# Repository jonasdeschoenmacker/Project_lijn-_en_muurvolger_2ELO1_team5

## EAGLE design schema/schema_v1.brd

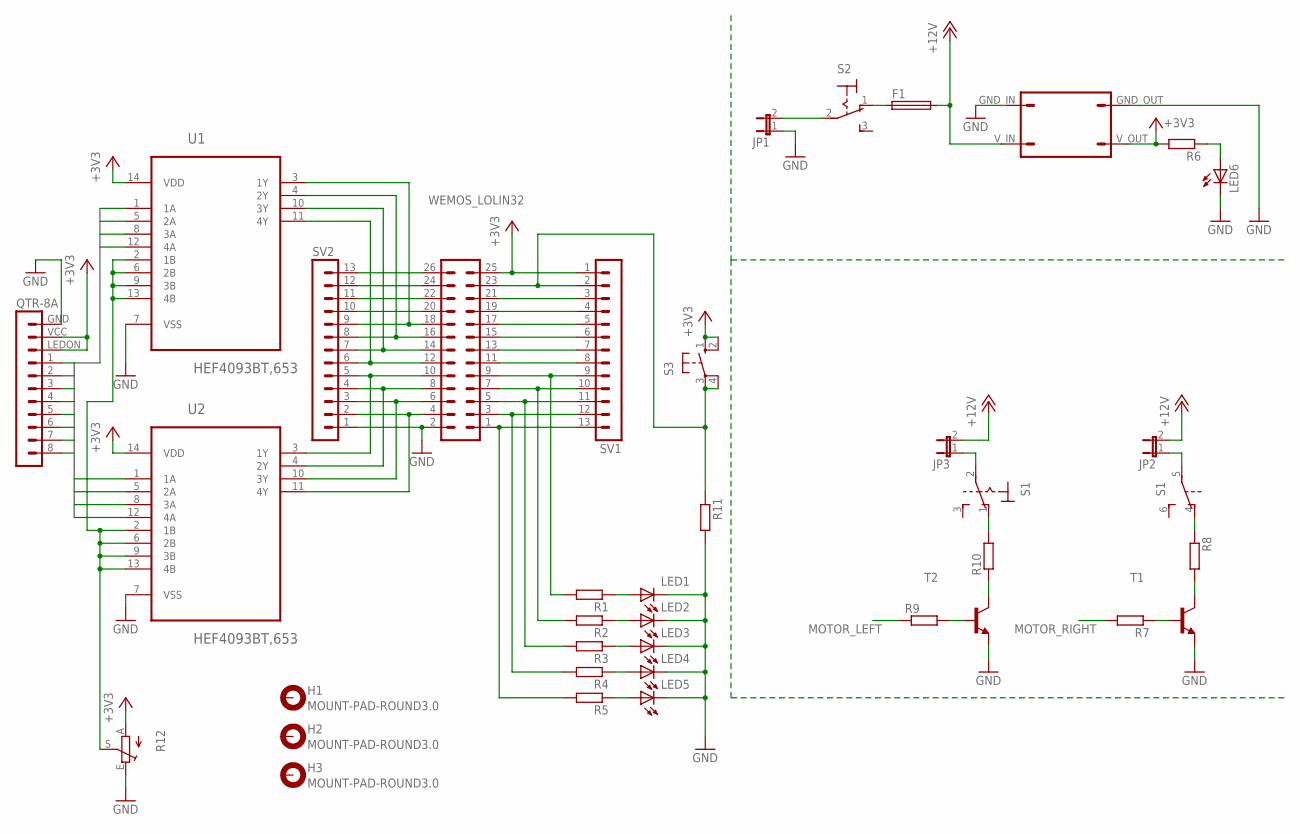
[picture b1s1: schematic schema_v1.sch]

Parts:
F1: SH22,5A
H1, H2, H3: MOUNT-PAD-ROUND3.0; 3,0-PAD
JP1, JP2, JP3: JP1E; JP1
LED1, LED2, LED3, LED4, LED5, LED6: LEDSMT1206; 1206
QTR-8A: WEMOS-LOLIN32_QTR-8A; WEMOS-LOLIN32_MA10-1
R1, R2, R3, R4, R5, R6, R7, R8, R9, R10, R11: R-EU_M0805; M0805
R12: POT_TRIM_EU-CA6V; POT_CA6V
S1: SWITCH_320-938
S2: SWITCH_320-916
S3: SWITCH-OMRON_10-XX; SWITCH-OMRON_B3F-10XX
SV1, SV2: MA13-1
T1, T2: TRANSISTOR-NPN-LINE-FOLLOWER_2N2222; TRANSISTOR-NPN-LINE-FOLLOWER_TO92-CBE
U1, U2: HEF4093BT,653; SOIC127P600X175-14N
U$2: COMPONENTEN-AANMAKEN_BUCK-CONVERTER; COMPONENTEN-AANMAKEN_MA04-1_BUCK
WEMOS_LOLIN32: WEMOS-LOLIN32_WEMOS_LOLIN32; WEMOS-LOLIN32_MA13-2

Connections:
+3V3: QTR-8A.LEDON, QTR-8A.VCC, R6.2, R12.A, S3.1 (S), S3.2 (S1), SV1.1, U1.14 (VDD), U2.14 (VDD), U$2.V_OUT, WEMOS_LOLIN32.25
+12V: F1.2, JP2.2, JP3.2, U$2.V_IN
ANALOG_BUS1: QTR-8A.1, U1.1 (1A)
ANALOG_BUS2: QTR-8A.2, U1.5 (2A)
ANALOG_BUS3: QTR-8A.3, U1.8 (3A)
ANALOG_BUS4: QTR-8A.4, U1.12 (4A)
ANALOG_BUS5: QTR-8A.5, U2.1 (1A)
ANALOG_BUS6: QTR-8A.6, U2.5 (2A)
ANALOG_BUS7: QTR-8A.7, U2.8 (3A)
ANALOG_BUS8: QTR-8A.8, U2.12 (4A)
GND: JP1.1, LED1.C, LED2.C, LED3.C, LED4.C, LED5.C, LED6.C, QTR-8A.GND, R11.2, R12.E, SV2.1, T1.E, T2.E, U1.7 (VSS), U2.7 (VSS), U$2.GND_IN, U$2.GND_OUT, WEMOS_LOLIN32.2
MOTOR_LEFT: R9.1, SV1.6, WEMOS_LOLIN32.15
MOTOR_RIGHT: R7.2, SV1.7, WEMOS_LOLIN32.13
unnamed: JP1.2, S2.2
unnamed: F1.1, S2.1 (O)
unnamed: SV2.9, U1.3 (1Y), WEMOS_LOLIN32.18
unnamed: LED6.A, R6.1
unnamed: SV2.8, U1.4 (2Y), WEMOS_LOLIN32.16
unnamed: SV2.7, U1.10 (3Y), WEMOS_LOLIN32.14
unnamed: SV2.6, U1.11 (4Y), WEMOS_LOLIN32.12
unnamed: SV2.2, U2.11 (4Y), WEMOS_LOLIN32.4
unnamed: LED1.A, R1.1
unnamed: LED2.A, R2.1
unnamed: LED3.A, R3.1
unnamed: LED4.A, R4.1
unnamed: LED5.A, R5.1
unnamed: R11.1, S3.3, S3.4 (P1), SV1.2, WEMOS_LOLIN32.23
unnamed: JP3.1, S1.2
unnamed: R10.2, S1.1 (O)
unnamed: R10.1, T2.C
unnamed: R9.2, T2.B
unnamed: JP2.1, S1.5
unnamed: R8.1, S1.4 (O)
unnamed: R8.2, T1.C
unnamed: R7.1, T1.B
unnamed: SV2.3, U2.10 (3Y), WEMOS_LOLIN32.6
unnamed: SV2.4, U2.4 (2Y), WEMOS_LOLIN32.8
unnamed: SV2.5, U2.3 (1Y), WEMOS_LOLIN32.10
unnamed: SV2.10, WEMOS_LOLIN32.20
unnamed: SV2.11, WEMOS_LOLIN32.22
unnamed: SV2.12, WEMOS_LOLIN32.24
unnamed: SV2.13, WEMOS_LOLIN32.26
unnamed: R5.2, SV1.13, WEMOS_LOLIN32.1
unnamed: R12.S, U1.2 (1B), U1.6 (2B), U1.9 (3B), U1.13 (4B), U2.2 (1B), U2.6 (2B), U2.9 (3B), U2.13 (4B)
unnamed: R4.2, SV1.12, WEMOS_LOLIN32.3
unnamed: R3.2, SV1.11, WEMOS_LOLIN32.5
unnamed: R2.2, SV1.10, WEMOS_LOLIN32.7
unnamed: R1.2, SV1.9, WEMOS_LOLIN32.9
unnamed: SV1.3, WEMOS_LOLIN32.21
unnamed: SV1.4, WEMOS_LOLIN32.19
unnamed: SV1.5, WEMOS_LOLIN32.17
unnamed: SV1.8, WEMOS_LOLIN32.11

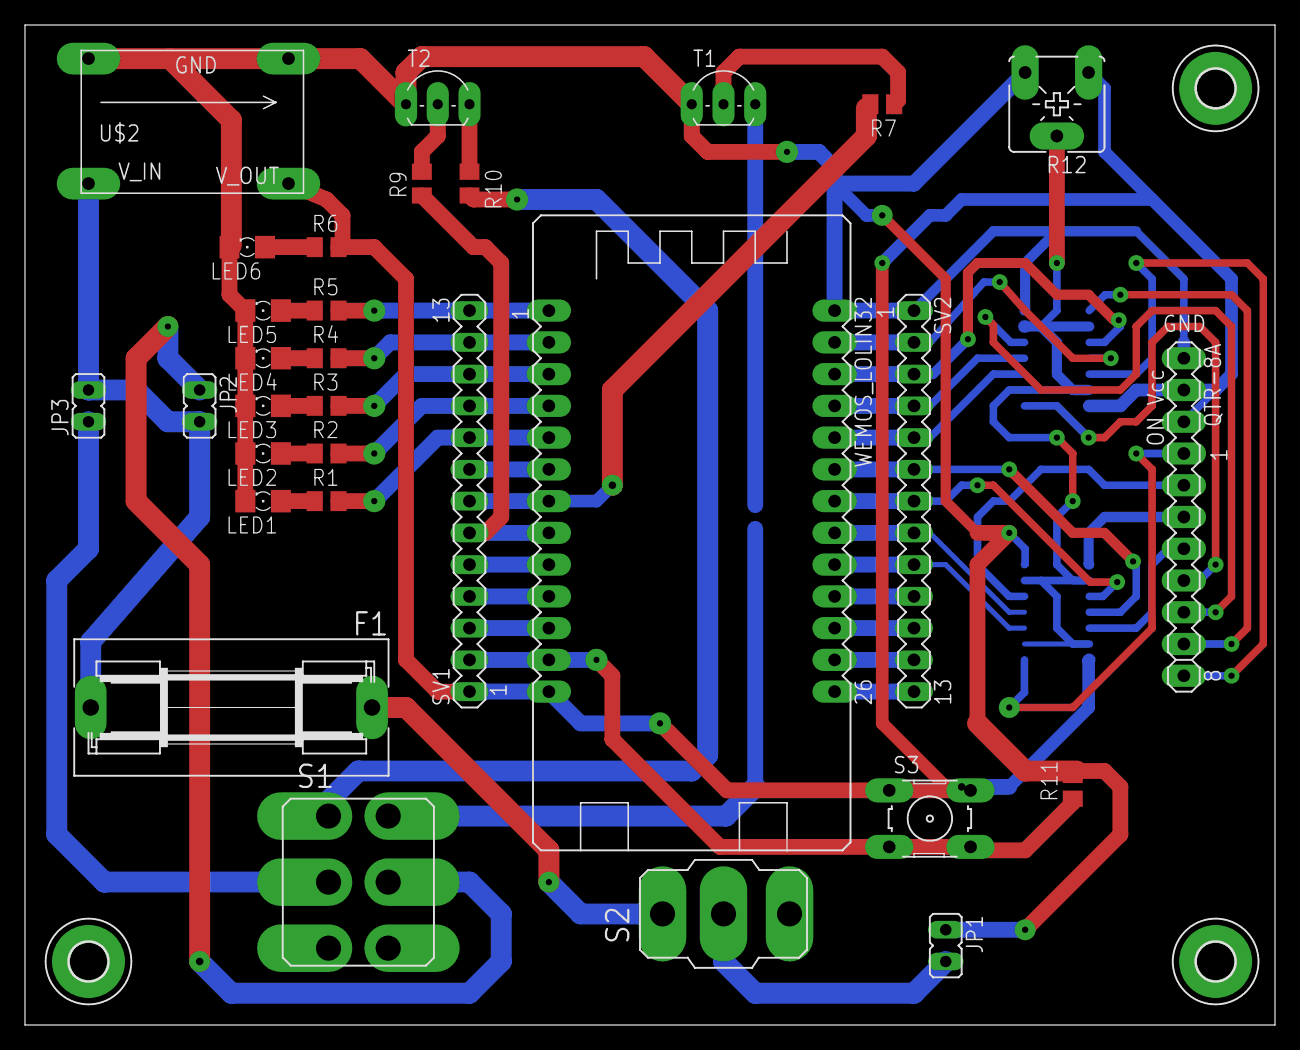
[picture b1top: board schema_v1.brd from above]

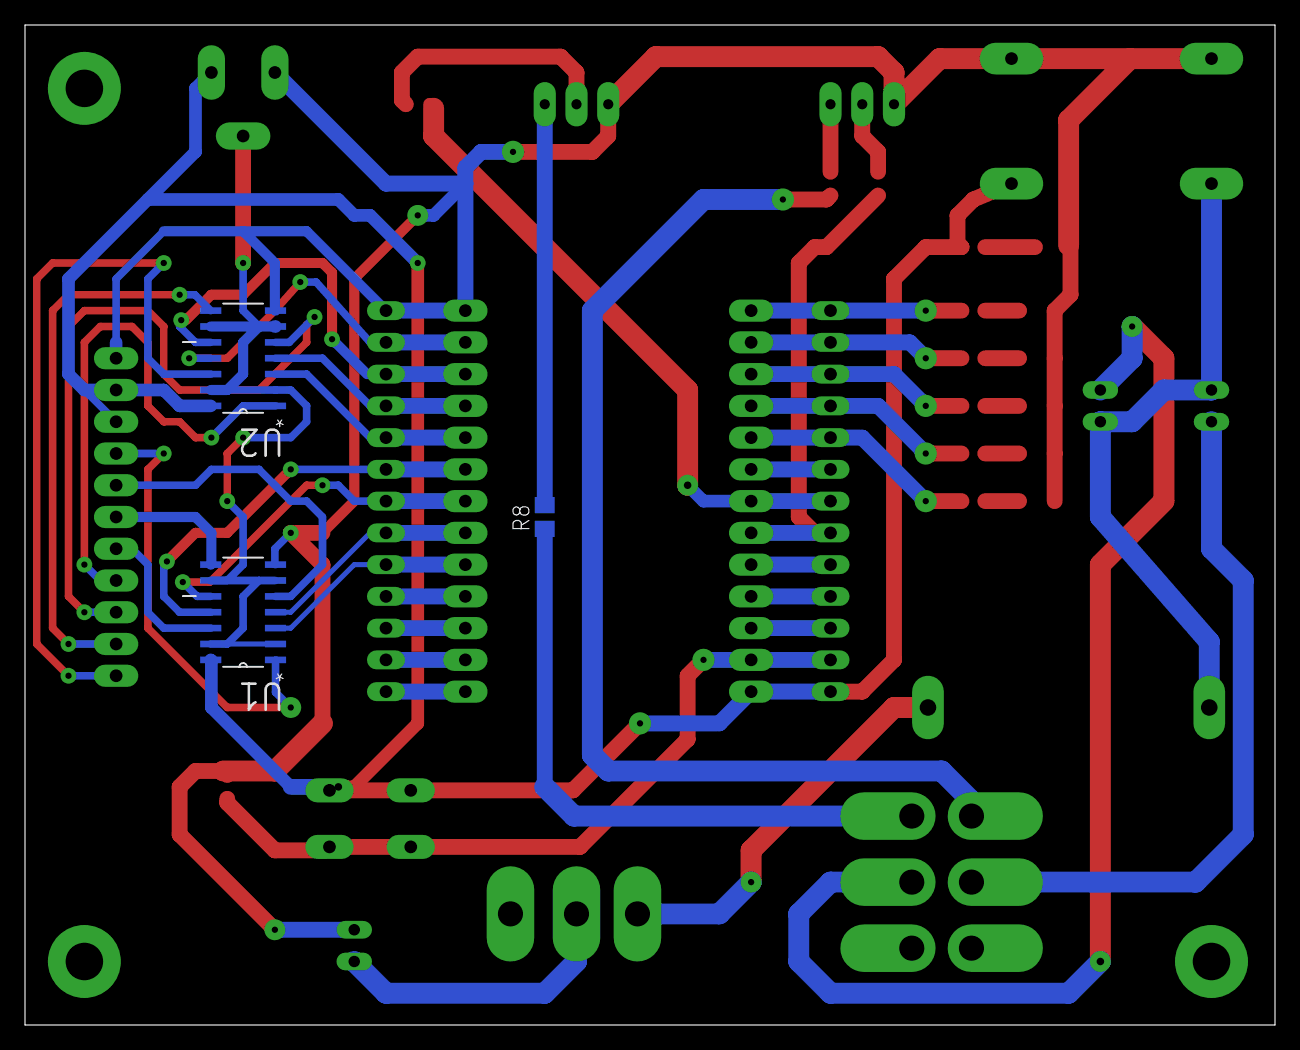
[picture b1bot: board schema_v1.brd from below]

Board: 2 copper layers, 100.0 x 80.0 mm, 37 parts (3 on the bottom side), 52 nets.

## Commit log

2018-03-07 Documenten
    Jonas De Schoenmacker documenten
